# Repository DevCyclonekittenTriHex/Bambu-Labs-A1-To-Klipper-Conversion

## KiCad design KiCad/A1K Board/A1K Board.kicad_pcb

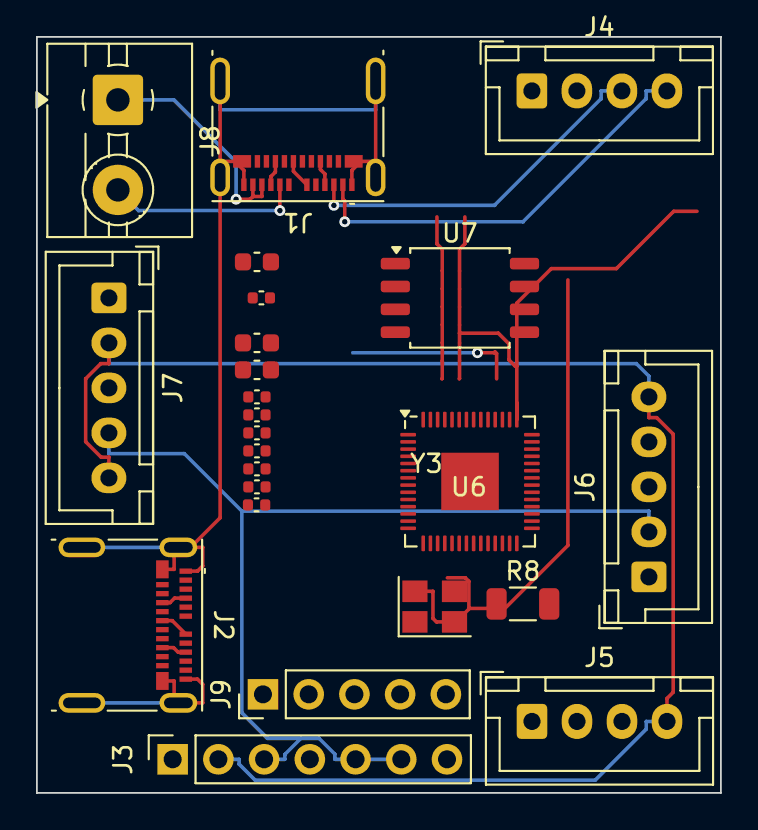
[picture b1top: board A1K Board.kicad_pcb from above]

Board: 2 copper layers, 38.0 x 42.0 mm, 24 parts (0 on the bottom side), 31 nets.

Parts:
C41, C42, C43, C44, C45, C46, C47, C50: 100nF; C_0402_1005Metric
C48, C51: 1uF; C_0603_1608Metric
C49: 10uF; C_0603_1608Metric
J1, J2: USB_C_Receptacle; USB_C_Receptacle_Molex_105450-0101
J3: Conn_01x07_Pin; PinSocket_1x07_P2.54mm_Vertical
J4: Motor; JST_XH_B4B-XH-A_1x04_P2.50mm_Vertical
J5: PCF; JST_XH_B4B-XH-A_1x04_P2.50mm_Vertical
J6: EXF; JST_XH_B5B-XH-A_1x05_P2.50mm_Vertical
J7: Biqu Probe; JST_XH_B5B-XH-A_1x05_P2.50mm_Vertical
J8: Screw_Terminal_01x02; TerminalBlock_MaiXu_MX126-5.0-02P_1x02_P5.00mm
J9: Conn_01x05_Pin; PinHeader_1x05_P2.54mm_Vertical
R8: 1kO; R_1206_3216Metric
U6: RP2040; QFN-56-1EP_7x7mm_P0.4mm_EP3.2x3.2mm
U7: W25Q16JVSS; SOIC-8_5.3x5.3mm_P1.27mm
Y3: Crystal_GND24; Crystal_SMD_3225-4Pin_3.2x2.5mm

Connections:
/Toolhead_Board/5V_BUS: J3.3, J3.5, J3.6, J6.2, J7.4
/Toolhead_Board/GND_BUS: J3.2, J5.4, J6.5, J7.2, J7.5
/Toolhead_Board/TH_RP2040/1V1_BUS: C50.2, C51.2, U6.23 (DVDD), U6.45 (VREG_VOUT), U6.50 (DVDD)
/Toolhead_Board/TH_RP2040/3V3_BUS: C41.2, C42.2, C43.2, C44.2, C45.2, C46.2, C47.2, C48.2, C49.2, U6.1 (IOVDD), U6.10 (IOVDD), U6.22 (IOVDD), U6.26 (RUN), U6.33 (IOVDD), U6.42 (IOVDD), U6.43 (ADC_AVDD), U6.44 (VREG_IN), U6.48 (USB_VDD), U6.49 (IOVDD), U7.8 (VCC)
/Toolhead_Board/TH_RP2040/GND_BUS: U6.19 (TESTEN), U6.57 (GND), U7.4 (GND), Y3.2, Y3.4
/Toolhead_Board/TH_RP2040/RP_PG_D+: J2.A6 (D+), J2.B6 (D+), U6.47 (USB_DP)
/Toolhead_Board/TH_RP2040/RP_PG_D-: J2.A7 (D-), J2.B7 (D-), U6.46 (USB_DM)
/Toolhead_Board/TH_RP2040/RP_USB_D+: J1.A6 (D+), J1.B6 (D+), U6.2 (GPIO0)
/Toolhead_Board/TH_RP2040/RP_USB_D-: J1.A7 (D-), J1.B7 (D-), U6.3 (GPIO1)
/Toolhead_Board/TH_RP2040/SD0: U6.53 (QSPI_SD0), U7.5 (DI/IO_{0})
/Toolhead_Board/TH_RP2040/SD1: U6.55 (QSPI_SD1), U7.2 (DO/IO_{1})
/Toolhead_Board/TH_RP2040/SD2: U6.54 (QSPI_SD2), U7.3 (~WP/IO_{2})
/Toolhead_Board/TH_RP2040/SD3: U6.51 (QSPI_SD3), U7.7 (~HOLD/~RESET/IO_{3})
/Toolhead_Board/TH_RP2040/SPI_CLK: U6.52 (QSPI_SCLK), U7.6 (CLK)
/Toolhead_Board/TH_RP2040/SPI_SS: U6.56 (QSPI_SS), U7.1 (~CS)
/Toolhead_Board/TH_RP2040/SWCLK: J9.1, U6.24 (SWCLK)
/Toolhead_Board/TH_RP2040/SWD: J9.2, U6.25 (SWD)
/Toolhead_Board/TH_USBC/5V_BUS: J2.A4 (VBUS), J2.A9 (VBUS), J2.B4 (VBUS), J2.B9 (VBUS)
/Toolhead_Board/TH_USBC/24V_BUS: J1.A4 (VBUS), J1.A9 (VBUS), J1.B4 (VBUS), J1.B9 (VBUS)
/Toolhead_Board/TH_USBC/GND_BUS: J1.A1 (GND), J1.A12 (GND), J1.B1 (GND), J1.B12 (GND), J1.S1 (SHIELD), J2.A1 (GND), J2.A12 (GND), J2.B1 (GND), J2.B12 (GND), J2.S1 (SHIELD)
/Toolhead_Board/TH_USBC/HOT_24V: J1.A8 (SBU1), J1.B2 (TX2+), J1.B8 (SBU2), J8.2
/Toolhead_Board/TH_USBC/HOT_GND: J1.A10 (RX2-), J1.A11 (RX2+), J1.B3 (TX2-), J8.1
/Toolhead_Board/TH_USBC/MOTOR_A1: J1.B10 (RX1-), J4.1
/Toolhead_Board/TH_USBC/MOTOR_A2: J1.B11 (RX1+), J4.2
/Toolhead_Board/TH_USBC/MOTOR_B1: J1.A3 (TX1-), J4.3
/Toolhead_Board/TH_USBC/MOTOR_B2: J1.A2 (TX1+), J4.4
unnamed: C41.1, C42.1, C43.1, C44.1, C45.1, C46.1, C47.1, C48.1, C49.1
unnamed: C50.1, C51.1
unnamed: R8.1, Y3.3
unnamed: U6.20 (XIN), Y3.1
unnamed: R8.2, U6.21 (XOUT)

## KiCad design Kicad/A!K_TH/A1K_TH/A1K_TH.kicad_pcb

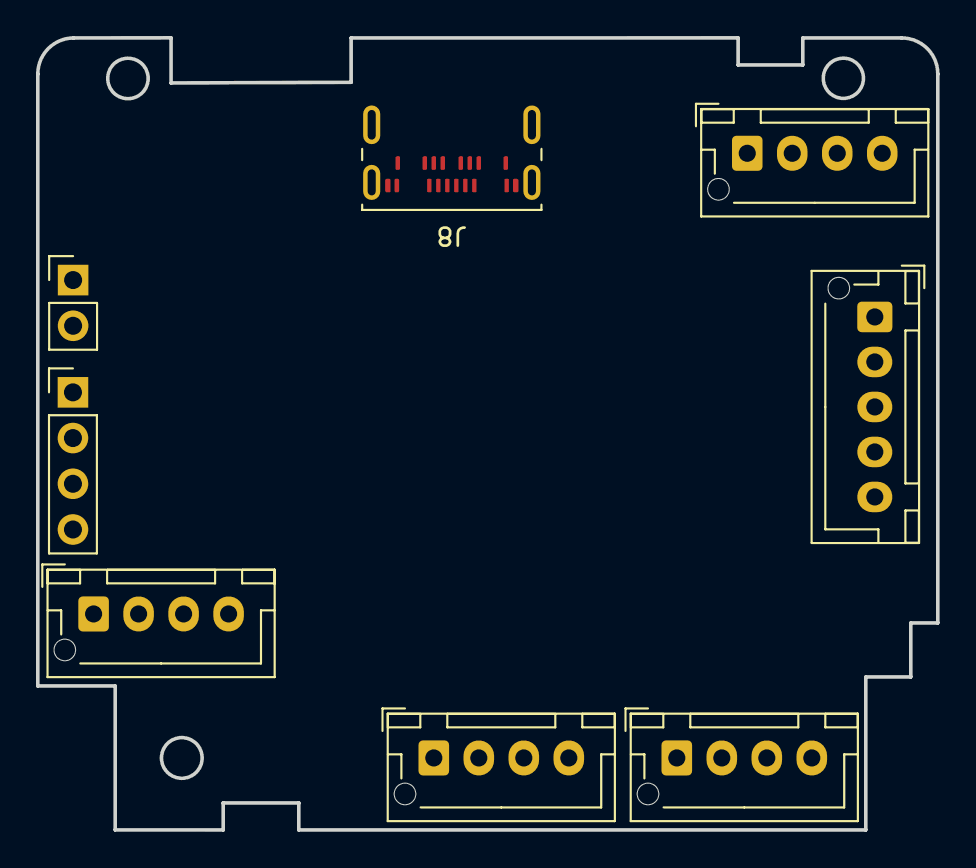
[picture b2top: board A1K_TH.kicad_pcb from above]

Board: 2 copper layers, 50.0 x 44.0 mm, 8 parts (0 on the bottom side), 2 nets, no tracks yet.

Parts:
J1: Extruder Motor; JST_XH_B4B-XH-AM_1x04_P2.50mm_Vertical
J2: Part Cooling Fan; JST_XH_B4B-XH-AM_1x04_P2.50mm_Vertical
J3: Extruder Fan; JST_XH_B5B-XH-AM_1x05_P2.50mm_Vertical
J4: Spare Fan; JST_XH_B4B-XH-AM_1x04_P2.50mm_Vertical
J5: BTT Eddy Coil; JST_XH_B4B-XH-AM_1x04_P2.50mm_Vertical
J6: HT & THRM; PinHeader_1x04_P2.54mm_Vertical
J7: FILSNR; PinHeader_1x02_P2.54mm_Vertical
J8: USB_C_Receptacle; USB_C_Receptacle_Amphenol_124019772112A

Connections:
unnamed: J8.A1 (GND), J8.A12 (GND), J8.B1 (GND), J8.B12 (GND)
unnamed: J8.A4 (VBUS), J8.A9 (VBUS), J8.B4 (VBUS), J8.B9 (VBUS)

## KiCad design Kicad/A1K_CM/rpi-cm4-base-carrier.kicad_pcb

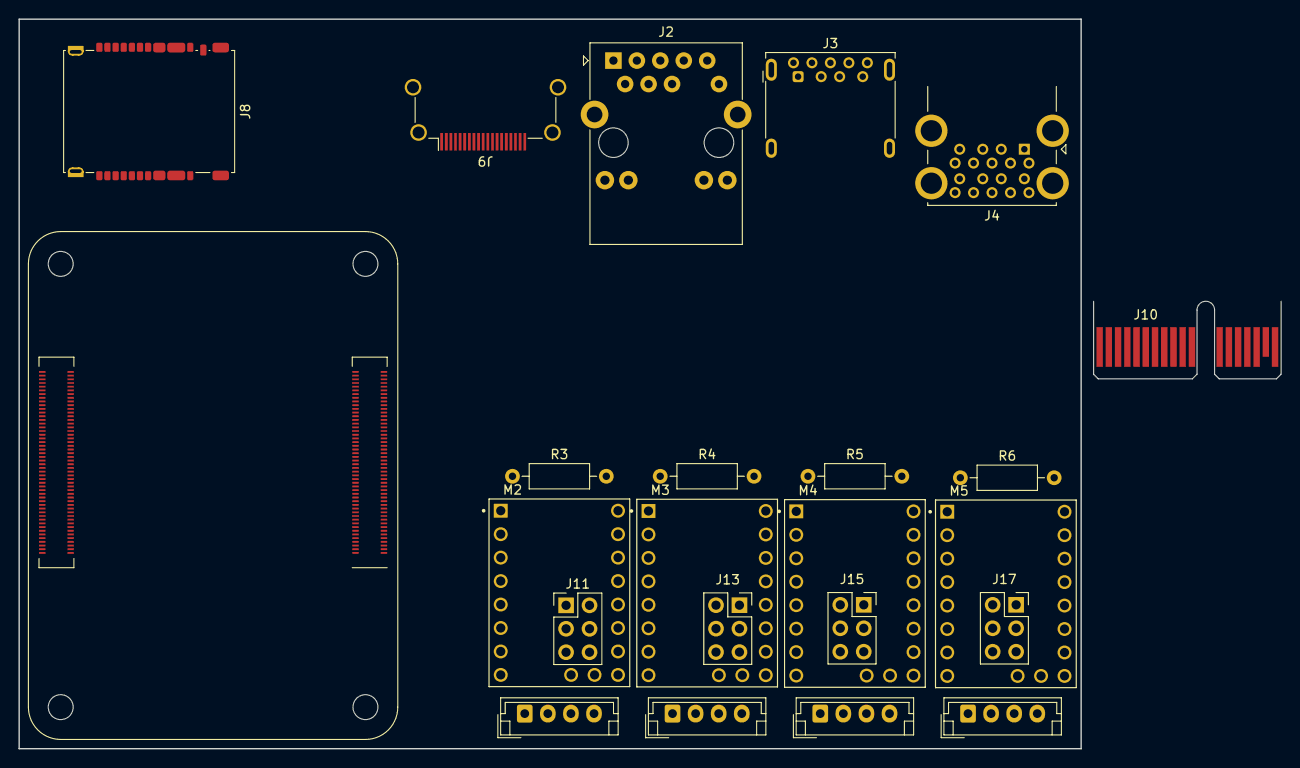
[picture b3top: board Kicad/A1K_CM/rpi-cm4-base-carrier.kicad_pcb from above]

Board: 2 copper layers, 115.0 x 79.0 mm, 23 parts (0 on the bottom side), 25 nets, no tracks yet.

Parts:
J1: X_MOTOR_JST; JST_EH_B4B-EH-A_1x04_P2.50mm_Vertical
J2: RJ45; RJ45_Abracon_ARJP11A-MA_Horizontal
J3: USB3_A; USB3_A_Molex_48393-001
J4: USB_A_Stacked; USB3_A_Molex_48406-0001_Horizontal_Stacked
J5: Y_MOTOR_JST; JST_EH_B4B-EH-A_1x04_P2.50mm_Vertical
J6: Z_MOTOR_JST; JST_EH_B4B-EH-A_1x04_P2.50mm_Vertical
J7: S_MOTOR_JST; JST_EH_B4B-EH-A_1x04_P2.50mm_Vertical
J8: Micro_SD_Card; SD-SIM_microSD-microSIM_Molex_104168-1620
J9: HDMI_A_1.4; HDMI_A_Amphenol_10029449-x01xLF_Horizontal
J10: Bus_PCI_Express_x1; BUS_PCIexpress_x1
J11: Conn_02x03_Odd_Even; PinHeader_2x03_P2.54mm_Vertical
J13, J15, J17: Conn_02x03_Odd_Even; PinSocket_2x03_P2.54mm_Vertical
M2, M3, M4, M5: TMC2209 Breakout; MODULE_TMC2209_SILENTSTEPSTICK
Module1: ComputeModule4-CM4; Raspberry-Pi-4-Compute-Module
R3, R4, R5, R6: 10kΩ; R_Axial_DIN0207_L6.3mm_D2.5mm_P10.16mm_Horizontal

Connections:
+1.8V: Module1.88 (+1.8v_(Output)), Module1.90 (+1.8v_(Output))
+3.3V: Module1.78 (GPIO_VREF(1.8v/3.3v_Input)), Module1.84 (+3.3v_(Output)), Module1.86 (+3.3v_(Output))
+3V3: M2.10 (VDD), M3.10 (VDD), M4.10 (VDD), M5.10 (VDD), R3.2, R4.2, R5.2, R6.2
+5V: Module1.77 (+5v_(Input)), Module1.79 (+5v_(Input)), Module1.81 (+5v_(Input)), Module1.83 (+5v_(Input)), Module1.85 (+5v_(Input)), Module1.87 (+5v_(Input))
/TMC Modules/CLK: J11.3, J13.3, J15.3, J17.3, M2.6 (CLK)
/TMC Modules/COIL-A1: M2.13 (A1), M3.13 (A1), M4.13 (A1), M5.13 (A1)
/TMC Modules/COIL-A2: M2.14 (A2), M3.14 (A2), M4.14 (A2), M5.14 (A2)
/TMC Modules/COIL-B1: M2.12 (B1), M3.12 (B1), M4.12 (B1), M5.12 (B1)
/TMC Modules/COIL-B2: M2.11 (B2), M3.11 (B2), M4.11 (B2), M5.11 (B2)
/TMC Modules/DIAG: J11.1, J13.1, J15.1, J17.1
/TMC Modules/PDN2: J11.6, J13.6, J15.6, J17.6, M2.5 (PDN2)
/TMC Modules/S_DIAG_INT: J17.2, J17.4, M5.18 (DIAG)
/TMC Modules/S_ENABLE: M5.1 (ENABLE), R6.1
/TMC Modules/VIN: M2.16 (VM), M3.16 (VM), M4.16 (VM), M5.16 (VM)
/TMC Modules/X_DIAG_INT: J11.2, J11.4, M2.18 (DIAG)
/TMC Modules/X_ENABLE: M2.1 (ENABLE), R3.1
/TMC Modules/Y_DIAG_INT: J13.2, J13.4, M3.18 (DIAG)
/TMC Modules/Y_ENABLE: M3.1 (ENABLE), R4.1
/TMC Modules/Z_DIAG_INT: J15.2, J15.4, M4.18 (DIAG)
/TMC Modules/Z_ENABLE: M4.1 (ENABLE), R5.1
GND: M2.9 (GND), M2.15 (GND), M3.9 (GND), M3.15 (GND), M4.9 (GND), M4.15 (GND), M5.9 (GND), M5.15 (GND), Module1.1 (GND), Module1.2 (GND), Module1.7 (GND), Module1.8 (GND), Module1.13 (GND), Module1.14 (GND), Module1.22 (GND), Module1.23 (GND), Module1.32 (GND), Module1.33 (GND), Module1.42 (GND), Module1.43 (GND), Module1.52 (GND), Module1.53 (GND), Module1.59 (GND), Module1.60 (GND), Module1.65 (GND), Module1.66 (GND), Module1.71 (GND), Module1.74 (GND), Module1.98 (GND), Module1.107 (GND), Module1.108 (GND), Module1.113 (GND), Module1.114 (GND), Module1.119 (GND), Module1.120 (GND), Module1.125 (GND), Module1.126 (GND), Module1.131 (GND), Module1.132 (GND), Module1.137 (GND), Module1.138 (GND), Module1.144 (GND), Module1.150 (GND), Module1.155 (GND), Module1.156 (GND), Module1.161 (GND), Module1.162 (GND), Module1.167 (GND), Module1.168 (GND), Module1.173 (GND), Module1.174 (GND), Module1.179 (GND), Module1.180 (GND), Module1.185 (GND), Module1.186 (GND), Module1.191 (GND), Module1.192 (GND), Module1.197 (GND), Module1.198 (GND)
unnamed: J10.A9 (+3.3V), J10.A10 (+3.3V), J10.B8 (+3.3V)
unnamed: J10.A2 (+12V), J10.A3 (+12V), J10.B1 (+12V), J10.B2 (+12V), J10.B3 (+12V)
unnamed: J10.A4 (GND), J10.A12 (GND), J10.A15 (GND), J10.A18 (GND), J10.B4 (GND), J10.B7 (GND), J10.B13 (GND), J10.B16 (GND), J10.B18 (GND)
SPI_MISO: J11.5, J13.5, J15.5, J17.5

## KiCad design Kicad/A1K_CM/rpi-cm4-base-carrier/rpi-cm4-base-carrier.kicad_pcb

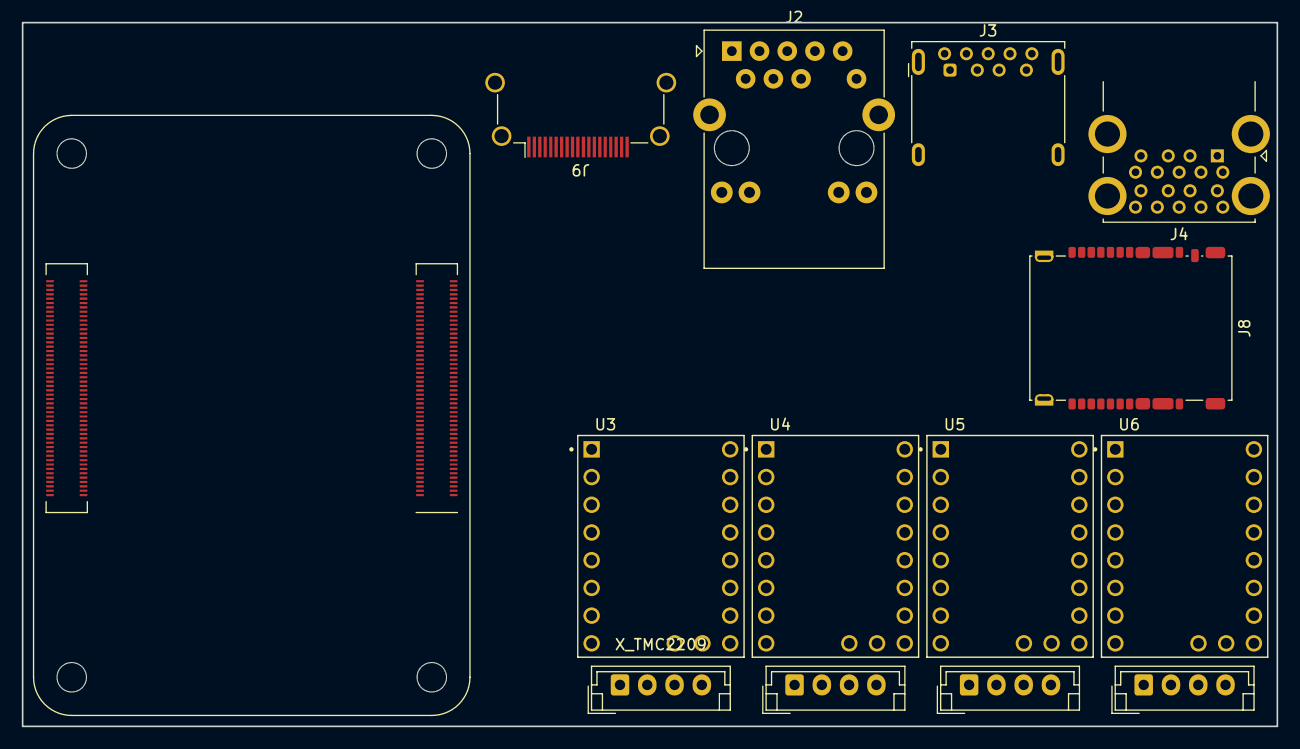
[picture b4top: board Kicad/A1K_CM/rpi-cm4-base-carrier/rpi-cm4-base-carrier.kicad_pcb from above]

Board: 2 copper layers, 115.0 x 64.5 mm, 14 parts (0 on the bottom side), 29 nets, no tracks yet.

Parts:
J1: X_MOTOR_JST; JST_EH_B4B-EH-A_1x04_P2.50mm_Vertical
J2: RJ45; RJ45_Abracon_ARJP11A-MA_Horizontal
J3: USB3_A; USB3_A_Molex_48393-001
J4: USB_A_Stacked; USB3_A_Molex_48406-0001_Horizontal_Stacked
J5: Y_MOTOR_JST; JST_EH_B4B-EH-A_1x04_P2.50mm_Vertical
J6: Z_MOTOR_JST; JST_EH_B4B-EH-A_1x04_P2.50mm_Vertical
J7: S_MOTOR_JST; JST_EH_B4B-EH-A_1x04_P2.50mm_Vertical
J8: Micro_SD_Card; SD-SIM_microSD-microSIM_Molex_104168-1620
J9: HDMI_A_1.4; HDMI_A_Amphenol_10029449-x01xLF_Horizontal
Module1: ComputeModule4-CM4; Raspberry-Pi-4-Compute-Module
U3, U4, U5, U6: X_TMC2209; MODULE_TMC2209_SILENTSTEPSTICK

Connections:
+1.8V: Module1.88 (+1.8v_(Output)), Module1.90 (+1.8v_(Output))
+3.3V: Module1.78 (GPIO_VREF(1.8v/3.3v_Input)), Module1.84 (+3.3v_(Output)), Module1.86 (+3.3v_(Output))
+5V: Module1.77 (+5v_(Input)), Module1.79 (+5v_(Input)), Module1.81 (+5v_(Input)), Module1.83 (+5v_(Input)), Module1.85 (+5v_(Input)), Module1.87 (+5v_(Input))
/CM4 GPIO/GPIO_5: Module1.34 (GPIO5), U3.10 (STEP), U4.10 (STEP), U5.10 (STEP), U6.10 (STEP)
/CM4 GPIO/GPIO_20: Module1.27 (GPIO20), U3.9 (DIR), U4.9 (DIR), U5.9 (DIR), U6.9 (DIR)
/TMC Modules/3V3_BUS: U3.2 (VIO), U3.14 (MS2), U3.15 (MS1), U4.2 (VIO), U4.14 (MS2), U4.15 (MS1), U5.2 (VIO), U5.14 (MS2), U5.15 (MS1), U6.2 (VIO), U6.14 (MS2), U6.15 (MS1)
/TMC Modules/24V_BUS: U3.8 (VM), U4.8 (VM), U5.8 (VM), U6.8 (VM)
/TMC Modules/GND_BUS: U3.1 (GND), U3.7 (GND), U4.1 (GND), U4.7 (GND), U5.1 (GND), U5.7 (GND), U6.1 (GND), U6.7 (GND)
/TMC Modules/M_EN: U3.16 (~EN), U4.16 (~EN), U5.16 (~EN), U6.16 (~EN)
/TMC Modules/M_PDN: U3.11 (PDN), U4.11 (PDN), U5.11 (PDN), U6.11 (PDN)
/TMC Modules/M_SPRD: U3.13 (SPRD), U4.13 (SPRD), U5.13 (SPRD), U6.13 (SPRD)
/TMC Modules/UART: U3.12 (UART), U4.12 (UART), U5.12 (UART), U6.12 (UART)
GND: Module1.1 (GND), Module1.2 (GND), Module1.7 (GND), Module1.8 (GND), Module1.13 (GND), Module1.14 (GND), Module1.22 (GND), Module1.23 (GND), Module1.32 (GND), Module1.33 (GND), Module1.42 (GND), Module1.43 (GND), Module1.52 (GND), Module1.53 (GND), Module1.59 (GND), Module1.60 (GND), Module1.65 (GND), Module1.66 (GND), Module1.71 (GND), Module1.74 (GND), Module1.98 (GND), Module1.107 (GND), Module1.108 (GND), Module1.113 (GND), Module1.114 (GND), Module1.119 (GND), Module1.120 (GND), Module1.125 (GND), Module1.126 (GND), Module1.131 (GND), Module1.132 (GND), Module1.137 (GND), Module1.138 (GND), Module1.144 (GND), Module1.150 (GND), Module1.155 (GND), Module1.156 (GND), Module1.161 (GND), Module1.162 (GND), Module1.167 (GND), Module1.168 (GND), Module1.173 (GND), Module1.174 (GND), Module1.179 (GND), Module1.180 (GND), Module1.185 (GND), Module1.186 (GND), Module1.191 (GND), Module1.192 (GND), Module1.197 (GND), Module1.198 (GND)
unnamed: J1.1, U3.4 (M1A)
unnamed: J1.2, U3.5 (M2A)
unnamed: J1.3, U3.3 (M1B)
unnamed: J1.4, U3.6 (M2B)
unnamed: J5.1, U4.4 (M1A)
unnamed: J5.2, U4.5 (M2A)
unnamed: J5.3, U4.3 (M1B)
unnamed: J5.4, U4.6 (M2B)
unnamed: J6.1, U5.4 (M1A)
unnamed: J6.2, U5.5 (M2A)
unnamed: J6.3, U5.3 (M1B)
unnamed: J6.4, U5.6 (M2B)
unnamed: J7.1, U6.4 (M1A)
unnamed: J7.2, U6.5 (M2A)
unnamed: J7.3, U6.3 (M1B)
unnamed: J7.4, U6.6 (M2B)

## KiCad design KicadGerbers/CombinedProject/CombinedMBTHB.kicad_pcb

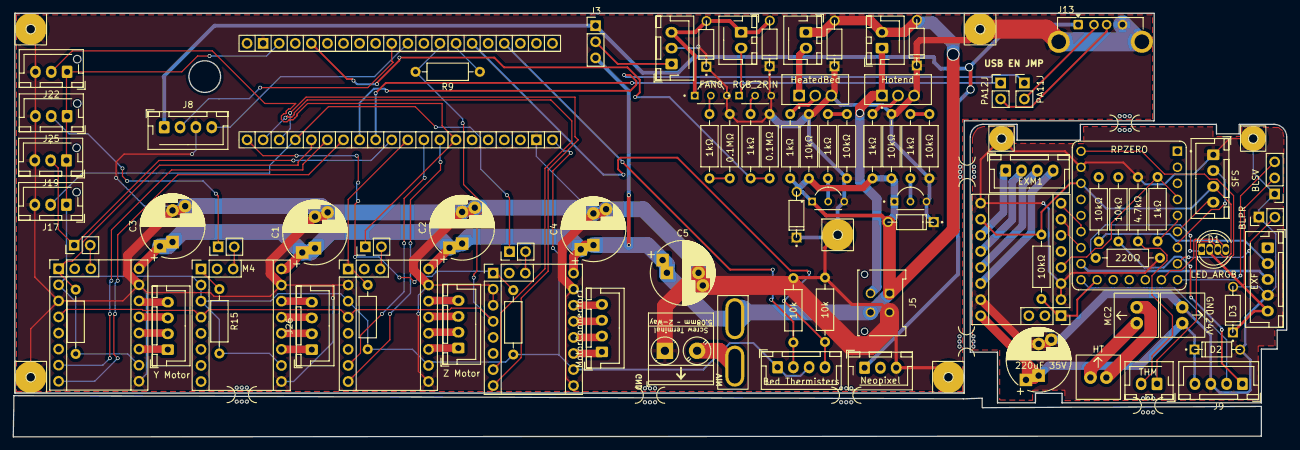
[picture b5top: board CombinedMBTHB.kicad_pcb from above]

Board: 2 copper layers, 201.2 x 66.9 mm, 103 parts (0 on the bottom side), 85 nets.

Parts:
C1, C2, C3, C4, C5: 220uF; CP_Radial_D10.0mm_P5.00mm_P7.50mm
C2#2: 220uF 35V; CP_Radial_D10.0mm_P5.00mm_P7.50mm
D1, D2, D3#2, D4, D5, D6: D; Diode
D1#2: LED_ARGB; LED_D5.0mm-4_RGB
D2#2: D_PCF; Diode
D3: D_EXF; Diode
EXM1: Conn_01x04; JST_XH_B4B-XH-A_1x04_P2.50mm_Vertical
F1: Mini ATO Fuse; Updated ATO Mini-Blade_2Post
H1, H1#2, H2, H2#2, H3, H4, H5: M1.5; Mountinghole_m1.5
J1: THM; JST_XH_B2B-XH-AM_1x02_P2.50mm_Vertical
J2: Neopixel; JST_XH_B3B-XH-AM_1x03_P2.50mm_Vertical
J2#2: SFS; JST_XH_B4B-XH-A_1x04_P2.50mm_Vertical
J3: FAN0_VS; PinHeader_1x03_P2.54mm_Vertical
J3#2: BLSV; PinHeader_1x03_P2.54mm_Vertical
J4: BLPR; PinHeader_1x02_P2.54mm_Vertical
J4#2: RGB_2PIN; JST_XH_B2B-XH-AM_1x02_P2.50mm_Vertical
J5: HT; ScrewTerminal 7mm x 7mm
J5#2: Molex 2x02 Microfit; Molex_Micro-Fit_3.0_43045-0412_2x02_P3.00mm_Vertical
J6: HeatedBed; JST_XH_B2B-XH-AM_1x02_P2.50mm_Vertical
J6#2: MC1; ScrewTerminal 7mm x 7mm
J7: MC2; ScrewTerminal 7mm x 7mm
J7#2: FAN0; JST_XH_B3B-XH-AM_1x03_P2.50mm_Vertical
J8: EXF; JST_XH_B5B-XH-AM_1x05_P2.50mm_Vertical
J8#2: SFS; JST_XH_B4B-XH-AM_1x04_P2.50mm_Vertical
J9: Hotend; JST_XH_B2B-XH-AM_1x02_P2.50mm_Vertical
J9#2: PCF; JST_XH_B4B-XH-A_1x04_P2.50mm_Vertical
J10: Screw_Terminal_01x02; 1x2 Terminal Block
J11: Bed Thermisters; JST_XH_B4B-XH-A_1x04_P2.50mm_Vertical
J13: USB_A; USB_A_Connfly_DS1095
J14: PA11J; PinHeader_1x02_P2.54mm_Vertical
J15: PA12J; PinHeader_1x02_P2.54mm_Vertical
J16, J18, J21, J24: SensorlessHoming; PinHeader_1x02_P2.54mm_Vertical
J17, J19, J22, J25: Endstop; JST_XH_B3B-XH-AM_1x03_P2.50mm_Vertical
J20, J23, J26: Conn_01x04; JST_XH_B4B-XH-A_1x04_P2.50mm_Vertical
M1: StepperMotor; TMC2209 Footprint
M1#2, M2, M3, M4: TMC2209 Breakout; TMC2209 Footprint
MotorConnector1: Conn_01x04; JST_XH_B4B-XH-A_1x04_P2.50mm_Vertical
Q5, Q7, Q9, Q10: 2n7000
Q6, Q8: NMOS; IRLZ44N
R1, R9, R17, R18, R21, R23, R25, R27: 1kΩ; R_Axial_DIN0207_L6.3mm_D2.5mm_P10.16mm_Horizontal
R2: 4.7kΩ; R_Axial_DIN0207_L6.3mm_D2.5mm_P10.16mm_Horizontal
R3: 220Ω; R_Axial_DIN0207_L6.3mm_D2.5mm_P10.16mm_Horizontal
R4, R5, R6, R12, R13, R14, R15, R16, R19, R20, R22: 10kΩ; R_Axial_DIN0207_L6.3mm_D2.5mm_P10.16mm_Horizontal
R10, R11: 10k; R_Axial_DIN0207_L6.3mm_D2.5mm_P10.16mm_Horizontal
R24, R26: 0.1MΩ; R_Axial_DIN0207_L6.3mm_D2.5mm_P10.16mm_Horizontal
RPZERO1: RPZERO; RP2040-ZERO
U1: STM32 Blackpill Socketed
mouse-bite-2.54mm-slot, mouse-bite-2.54mm-slot#2, mouse-bite-2.54mm-slot#3, mouse-bite-2.54mm-slot#4, mouse-bite-2.54mm-slot#5, mouse-bite-2.54mm-slot#6, mouse-bite-2.54mm-slot#7: VAL**; mouse-bite-2.54mm-slot

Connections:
5V: D1.2 (A), D2.2 (A), J4#2.1, J7#2.3, Q9.1 (D)
+3V3: D1#2.3 (GK), J1.1, J2#2.3, J11.1, J11.3, J17.1, J19.1, J22.1, J25.1, M1.10 (VDD), M1#2.10 (VDD), M2.2 (MS1), M2.10 (VDD), M3.3 (MS2), M3.10 (VDD), M4.2 (MS1), M4.3 (MS2), M4.10 (VDD), R6.2, R12.2, R13.2, R14.2, R15.2, RPZERO1.21 (3V3), U1.18 (3V3), U1.40 (3V3)
+5V: D1#2.2 (RK), D3.1 (K), J2.1, J3.1, J3#2.2, J8.5, J8#2.1, J13.1 (VBUS), RPZERO1.23 (5V)
+24V: C1.1, C2.1, C2#2.1, C3.1, C4.1, C5.1, D2#2.1 (K), D3#2.2 (A), D4.2 (A), D5.2 (A), D6.2 (A), F1.1, J3.3, J5#2.1, J5#2.4, J6.1, J6#2.1, J9.2, J9#2.4, M1.16 (VM), M1#2.16 (VM), M2.16 (VM), M3.16 (VM), M4.16 (VM), Q5.1 (D), Q7.1 (D), R18.1, R19.1, R22.1, R23.1
/ HEATED_BED_PIN: R20.1, R21.1
/BED_THM_1: J11.4, R10.1, U1.6 (PA0)
/BED_THM_2: J11.2, R11.1, U1.4 (PC15)
/BL_PR: J4.2, RPZERO1.8 (GP7)
/BL_SV: J3#2.3, RPZERO1.9 (GP8)
/D+: J13.3 (D+), J15.2
/D-: J13.2 (D-), J14.2
/EMotor/A1: J26.3, M4.13 (A1)
/EMotor/A2: J26.4, M4.14 (A2)
/EMotor/B1: J26.2, M4.12 (B1)
/EMotor/B2: J26.1, M4.11 (B2)
/EXF_SG: J8.3, RPZERO1.16 (GP15)
/ExtruderDriver/A1: EXM1.3, M1.13 (A1)
/ExtruderDriver/A2: EXM1.4, M1.14 (A2)
/ExtruderDriver/B1: EXM1.2, M1.12 (B1)
/ExtruderDriver/B2: EXM1.1, M1.11 (B2)
/FAN0_PIN: R24.1, R25.1
/HEATER_PIN: R16.1, R17.1
/LED_TEST: D1#2.4 (BK), RPZERO1.10 (GP9)
/ME_DIAG: J24.1, J25.2
/ME_EN: M4.1 (ENABLE), R15.1
/MX_DIAG: J16.1, J17.2, U1.24 (PB15)
/MX_DIR: M1#2.8 (DIR), U1.23 (PB14)
/MX_EN: M1#2.1 (ENABLE), R12.1, U1.21 (PB12)
/MX_STEP: M1#2.7 (STEP), U1.22 (PB13)
/MY_DIAG: J18.1, J19.2, U1.30 (PA15)
/MY_DIR: M2.8 (DIR), U1.27 (PA10)
/MY_EN: M2.1 (ENABLE), R13.1, U1.25 (PA8)
/MY_STEP: M2.7 (STEP), U1.26 (PA9)
/MZ_DIAG: J21.1, J22.2, U1.34 (PB6)
/MZ_DIR: M3.8 (DIR), U1.33 (PB5)
/MZ_EN: M3.1 (ENABLE), R14.1, U1.31 (PB3)
/MZ_STEP: M3.7 (STEP), U1.32 (PB4)
/M_DIR: M1.8 (DIR), RPZERO1.18 (GP27)
/M_EN: M1.1 (ENABLE), R6.1, RPZERO1.14 (GP13)
/M_STEP: M1.7 (STEP), RPZERO1.17 (GP26)
/M_UART: M1.4 (PDN1), M1#2.4 (PDN1), M2.4 (PDN1), M3.4 (PDN1), M4.4 (PDN1), R1.1, R9.2, RPZERO1.4 (GP3), U1.8 (PA2)
/Mosfet1/Output_Return: J6.2, Q8.1 (D)
/Mosfet/Output_Return: J5#2.3, J9.1, Q6.1 (D)
/OpticSensor: J8#2.4, U1.10 (PA4)
/PA11: J14.1, U1.28 (PA11)
/PA12: J15.1, U1.29 (PA12)
/PCF_SG: J9#2.2, RPZERO1.15 (GP14)
/RGB_PIN: R26.1, R27.1, U1.16 (PB2)
/SFS_ENC: J2#2.2, RPZERO1.7 (GP6)
/SFS_SW: J2#2.4, RPZERO1.6 (GP5)
/SwitchSensor: J8#2.2, U1.11 (PA5)
/TH_SG: J1.2, R2.1
/Transistor1/Output_GND: J4#2.2, Q10.1 (D)
/UART_RX: R9.1, U1.7 (PA1)
/XMotor/A1: M1#2.13 (A1), MotorConnector1.3
/XMotor/A2: M1#2.14 (A2), MotorConnector1.4
/XMotor/B1: M1#2.12 (B1), MotorConnector1.2
/XMotor/B2: M1#2.11 (B2), MotorConnector1.1
/YMotor/A1: J20.3, M2.13 (A1)
/YMotor/A2: J20.4, M2.14 (A2)
/YMotor/B1: J20.2, M2.12 (B1)
/YMotor/B2: J20.1, M2.11 (B2)
/ZMotor/A1: J23.3, M3.13 (A1)
/ZMotor/A2: J23.4, M3.14 (A2)
/ZMotor/B1: J23.2, M3.12 (B1)
/ZMotor/B2: J23.1, M3.11 (B2)
GND: C1.2, C2.2, C2#2.2, C3.2, C4.2, C5.2, D1.1 (K), D2.1 (K), D2#2.2 (A), D3.2 (A), D3#2.1 (K), D4.1 (K), D5.1 (K), D6.1 (K), H1.1, H1#2.1, H2.1, H2#2.1, H3.1, H4.1, H5.1, J2.3, J2#2.1, J3#2.1, J4.1, J5#2.2, J6#2.2, J7#2.2, J8.4, J8#2.3, J9#2.3, J10.1, J13.4 (GND), J13.5 (Shield), J17.3, J19.3, J22.3, J25.3, M1.2 (MS1), M1.3 (MS2), M1.9 (GND), M1.15 (GND), M1#2.2 (MS1), M1#2.3 (MS2), M1#2.9 (GND), M1#2.15 (GND), M2.3 (MS2), M2.9 (GND), M2.15 (GND), M3.2 (MS1), M3.9 (GND), M3.15 (GND), M4.9 (GND), M4.15 (GND), Q5.3 (S), Q6.3 (S), Q7.3 (S), Q8.3 (S), Q9.3 (S), Q10.3 (S), R2.2, R3.2, R10.2, R11.2, R16.2, R19.2, R20.2, R22.2, R24.2, R26.2, RPZERO1.22 (GND), U1.19 (GND), U1.39 (GND)
unnamed: D1#2.1 (A), R3.1
unnamed: J3.2, J7#2.1
unnamed: J5.1, J7.1
unnamed: J5.2, J7.2
unnamed: J8.2, R5.1
unnamed: J9#2.1, R4.1
unnamed: F1.2, J10.2
unnamed: J16.2, M1#2.18 (DIAG)
unnamed: J18.2, M2.18 (DIAG)
unnamed: J21.2, M3.18 (DIAG)
unnamed: J24.2, M4.18 (DIAG)
unnamed: Q5.2 (G), R17.2
unnamed: Q6.2 (G), R18.2
unnamed: Q7.2 (G), R21.2
unnamed: Q8.2 (G), R23.2
unnamed: Q9.2 (G), R25.2
unnamed: Q10.2 (G), R27.2
unnamed: R1.2, RPZERO1.5 (GP4)

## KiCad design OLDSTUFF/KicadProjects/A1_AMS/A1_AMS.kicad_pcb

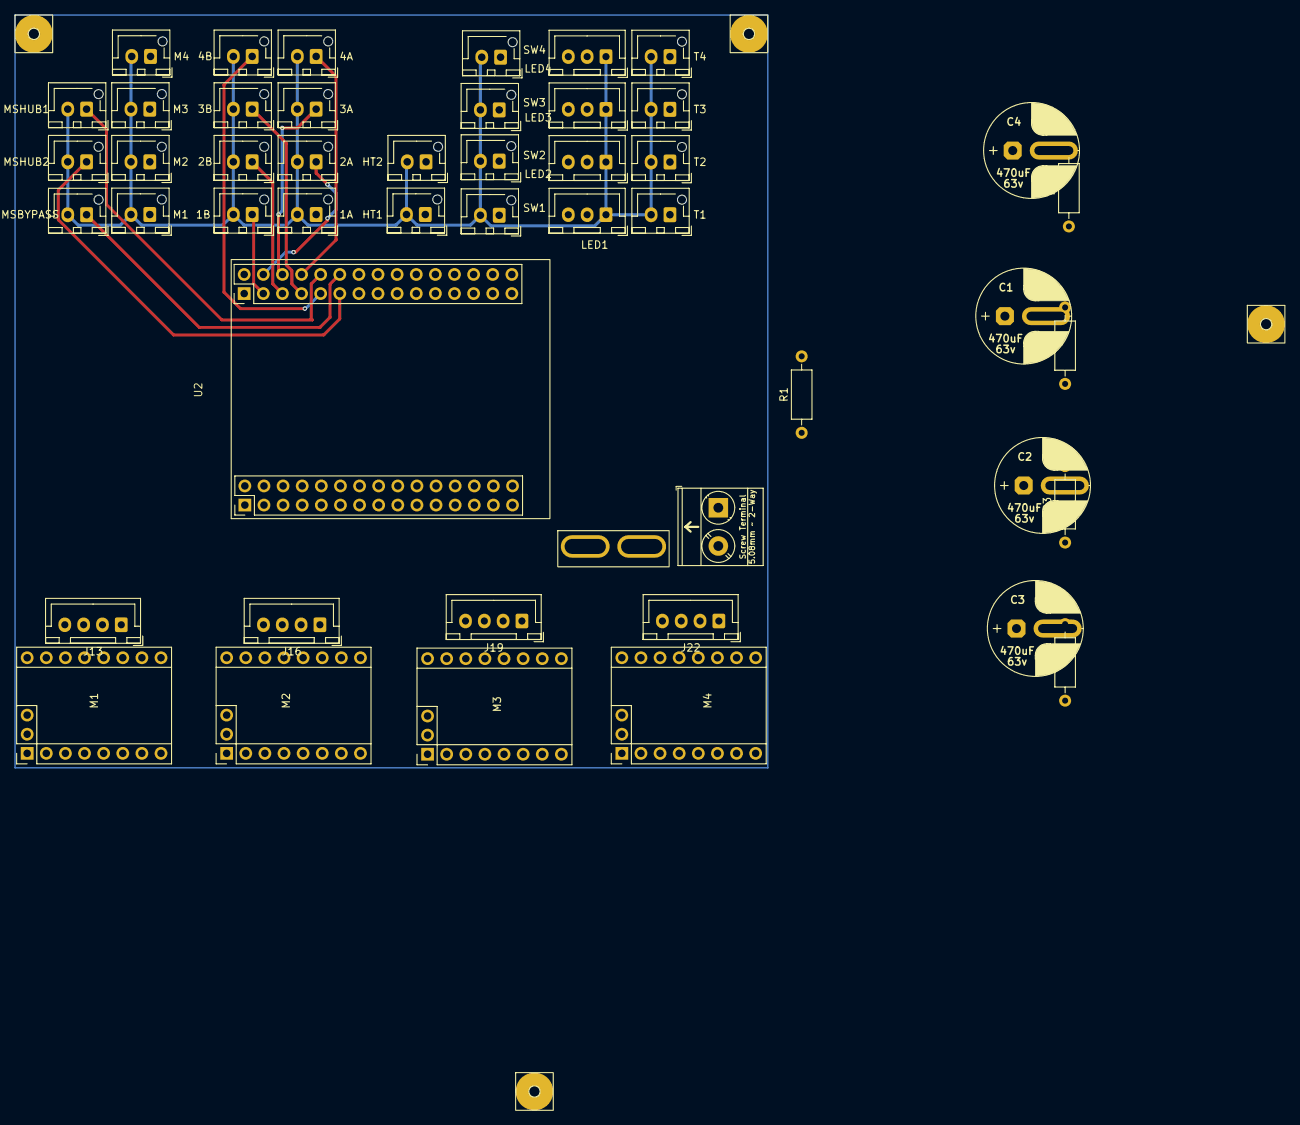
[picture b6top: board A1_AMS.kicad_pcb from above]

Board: 2 copper layers, 53 parts (0 on the bottom side), 60 nets.

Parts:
C1, C2, C3, C4: 470uF; Cap ~ 12.5, 2.5mm-7.5mm pitch
F1: Mini ATO Fuse; Updated ATO Mini-Blade_2Post
H1, H2, H4, H5: M1.5; Mountinghole_m1.5
J1: 1A; JST_XH_B2B-XH-AM_1x02_P2.50mm_Vertical
J2: 2A; JST_XH_B2B-XH-AM_1x02_P2.50mm_Vertical
J3: 3A; JST_XH_B2B-XH-AM_1x02_P2.50mm_Vertical
J4: 4A; JST_XH_B2B-XH-AM_1x02_P2.50mm_Vertical
J5: LED1; JST_XH_B3B-XH-A_1x03_P2.50mm_Vertical
J6: 1B; JST_XH_B2B-XH-AM_1x02_P2.50mm_Vertical
J7: 2B; JST_XH_B2B-XH-AM_1x02_P2.50mm_Vertical
J8: 3B; JST_XH_B2B-XH-AM_1x02_P2.50mm_Vertical
J9: 4B; JST_XH_B2B-XH-AM_1x02_P2.50mm_Vertical
J10: Screw_Terminal_01x02; 1x2 Terminal Block
J11: M1; JST_XH_B2B-XH-AM_1x02_P2.50mm_Vertical
J12: M2; JST_XH_B2B-XH-AM_1x02_P2.50mm_Vertical
J13, J16, J19, J22: Conn_01x04; JST_XH_B4B-XH-A_1x04_P2.50mm_Vertical
J14: M4; JST_XH_B2B-XH-AM_1x02_P2.50mm_Vertical
J15: M3; JST_XH_B2B-XH-AM_1x02_P2.50mm_Vertical
J17: LED2; JST_XH_B3B-XH-A_1x03_P2.50mm_Vertical
J18: LED3; JST_XH_B3B-XH-A_1x03_P2.50mm_Vertical
J20: LED4; JST_XH_B3B-XH-A_1x03_P2.50mm_Vertical
J21: SW1; JST_XH_B2B-XH-AM_1x02_P2.50mm_Vertical
J23: SW2; JST_XH_B2B-XH-AM_1x02_P2.50mm_Vertical
J24: SW3; JST_XH_B2B-XH-AM_1x02_P2.50mm_Vertical
J25: MSHUB1; JST_XH_B2B-XH-AM_1x02_P2.50mm_Vertical
J26: MSHUB2; JST_XH_B2B-XH-AM_1x02_P2.50mm_Vertical
J27: MSBYPASS; JST_XH_B2B-XH-AM_1x02_P2.50mm_Vertical
J29: T1; JST_XH_B2B-XH-AM_1x02_P2.50mm_Vertical
J30: T2; JST_XH_B2B-XH-AM_1x02_P2.50mm_Vertical
J31: T3; JST_XH_B2B-XH-AM_1x02_P2.50mm_Vertical
JS4: SW4; JST_XH_B2B-XH-AM_1x02_P2.50mm_Vertical
JS5: T4; JST_XH_B2B-XH-AM_1x02_P2.50mm_Vertical
JS6: HT1; JST_XH_B2B-XH-AM_1x02_P2.50mm_Vertical
JS7: HT2; JST_XH_B2B-XH-AM_1x02_P2.50mm_Vertical
M1, M2, M3, M4: TMC2209 Breakout; TMC2209 Footprint
R1: 1kΩ; R_Axial_DIN0207_L6.3mm_D2.5mm_P10.16mm_Horizontal
R2, R3, R4, R5: 10kΩ; R_Axial_DIN0207_L6.3mm_D2.5mm_P10.16mm_Horizontal
U2: Socketed MCU STM32 64P

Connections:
+3V3: M1.10 (VDD), M2.10 (VDD), M3.10 (VDD), M4.10 (VDD), R2.2, R3.2, R4.2, R5.2
/3V3: M2.2 (MS1), M3.3 (MS2), M4.2 (MS1), M4.3 (MS2)
/5V: J5.3, J17.3, J18.3, J20.3
/AMotor/A1: J13.3, M1.13 (A1)
/AMotor/A2: J13.4, M1.14 (A2)
/AMotor/B1: J13.2, M1.12 (B1)
/AMotor/B2: J13.1, M1.11 (B2)
/BMotor/A1: J16.3, M2.13 (A1)
/BMotor/A2: J16.4, M2.14 (A2)
/BMotor/B1: J16.2, M2.12 (B1)
/BMotor/B2: J16.1, M2.11 (B2)
/CMotor/A1: J19.3, M3.13 (A1)
/CMotor/A2: J19.4, M3.14 (A2)
/CMotor/B1: J19.2, M3.12 (B1)
/CMotor/B2: J19.1, M3.11 (B2)
/DMotor/A1: J22.3, M4.13 (A1)
/DMotor/A2: J22.4, M4.14 (A2)
/DMotor/B1: J22.2, M4.12 (B1)
/DMotor/B2: J22.1, M4.11 (B2)
/HT_C1: JS6.1, U2.43 (PA12)
/HT_C2: JS7.1, U2.44 (PA15)
/LED_1: J5.2, U2.49 (PC8)
/LED_2: J17.2, U2.50 (PC9)
/LED_3: J18.2, U2.51 (PC6)
/LED_4: J20.2, U2.52 (PC7)
/MA_DIR: M1.8 (DIR), U2.5 (PC0)
/MA_EN: M1.1 (ENABLE), R2.1, U2.3 (PC14)
/MA_STEP: M1.7 (STEP), U2.4 (PC13)
/MB_DIR: M2.8 (DIR), U2.8 (PC1)
/MB_EN: M2.1 (ENABLE), R3.1, U2.6 (PC15)
/MB_STEP: M2.7 (STEP), U2.7 (PC2)
/MC_DIR: M3.8 (DIR), U2.11 (PA2)
/MC_EN: M3.1 (ENABLE), R4.1, U2.9 (PA0)
/MC_STEP: M3.7 (STEP), U2.10 (PC3)
/MD_DIR: M4.8 (DIR), U2.14 (PA3)
/MD_EN: M4.1 (ENABLE), R5.1, U2.12 (PA1)
/MD_STEP: M4.7 (STEP), U2.13 (PA4)
/MS_1A: J1.1, U2.31 (PB9)
/MS_1B: J6.1, U2.33 (PB7)
/MS_2A: J2.1, U2.34 (PB8)
/MS_2B: J7.1, U2.35 (PB5)
/MS_3A: J3.1, U2.36 (PB6)
/MS_3B: J8.1, U2.37 (PB3)
/MS_4A: J4.1, U2.38 (PB4)
/MS_4B: J9.1, U2.39 (PC12)
/MS_BYPASS: J27.1, U2.42 (PC11)
/MS_HUB1: J25.1, U2.40 (PD2)
/MS_HUB2: J26.1, U2.41 (PC10)
/M_UART: M1.4 (PDN1), M2.4 (PDN1), M4.4 (PDN1), R1.2
/M_VBUS: C1.1, C2.1, C3.1, C4.1, F1.1, M1.16 (VM), M2.16 (VM), M3.16 (VM), M4.16 (VM)
/SW_1: J21.1, U2.45 (PA10)
/SW_2: J23.1, U2.46 (PA11)
/SW_3: J24.1, U2.47 (PA8)
/SW_4: JS4.1, U2.48 (PA9)
/THM_1: J29.1, U2.53 (PB14)
/THM_2: J30.1, U2.54 (PB15)
/THM_3: J31.1, U2.55 (PB12)
/THM_4: JS5.1, U2.56 (PB13)
/VIN: F1.2, J10.2
GND: C1.2, C2.2, C3.2, C4.2, H1.1, H2.1, H4.1, H5.1, J1.2, J2.2, J3.2, J4.2, J5.1, J6.2, J7.2, J8.2, J9.2, J10.1, J11.2, J12.2, J14.2, J15.2, J17.1, J18.1, J20.1, J21.2, J23.2, J24.2, J25.2, J26.2, J27.2, J29.2, J30.2, J31.2, JS4.2, JS5.2, JS6.2, JS7.2, M1.2 (MS1), M1.3 (MS2), M1.9 (GND), M1.15 (GND), M2.3 (MS2), M2.9 (GND), M2.15 (GND), M3.2 (MS1), M3.9 (GND), M3.15 (GND), M4.9 (GND), M4.15 (GND)

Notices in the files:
Kicad/A1K_CM/rpi-cm4-base-carrier.kicad_pcb:
creativecommons.org/licenses/by/4.0
License: CC BY-SA 4.0
